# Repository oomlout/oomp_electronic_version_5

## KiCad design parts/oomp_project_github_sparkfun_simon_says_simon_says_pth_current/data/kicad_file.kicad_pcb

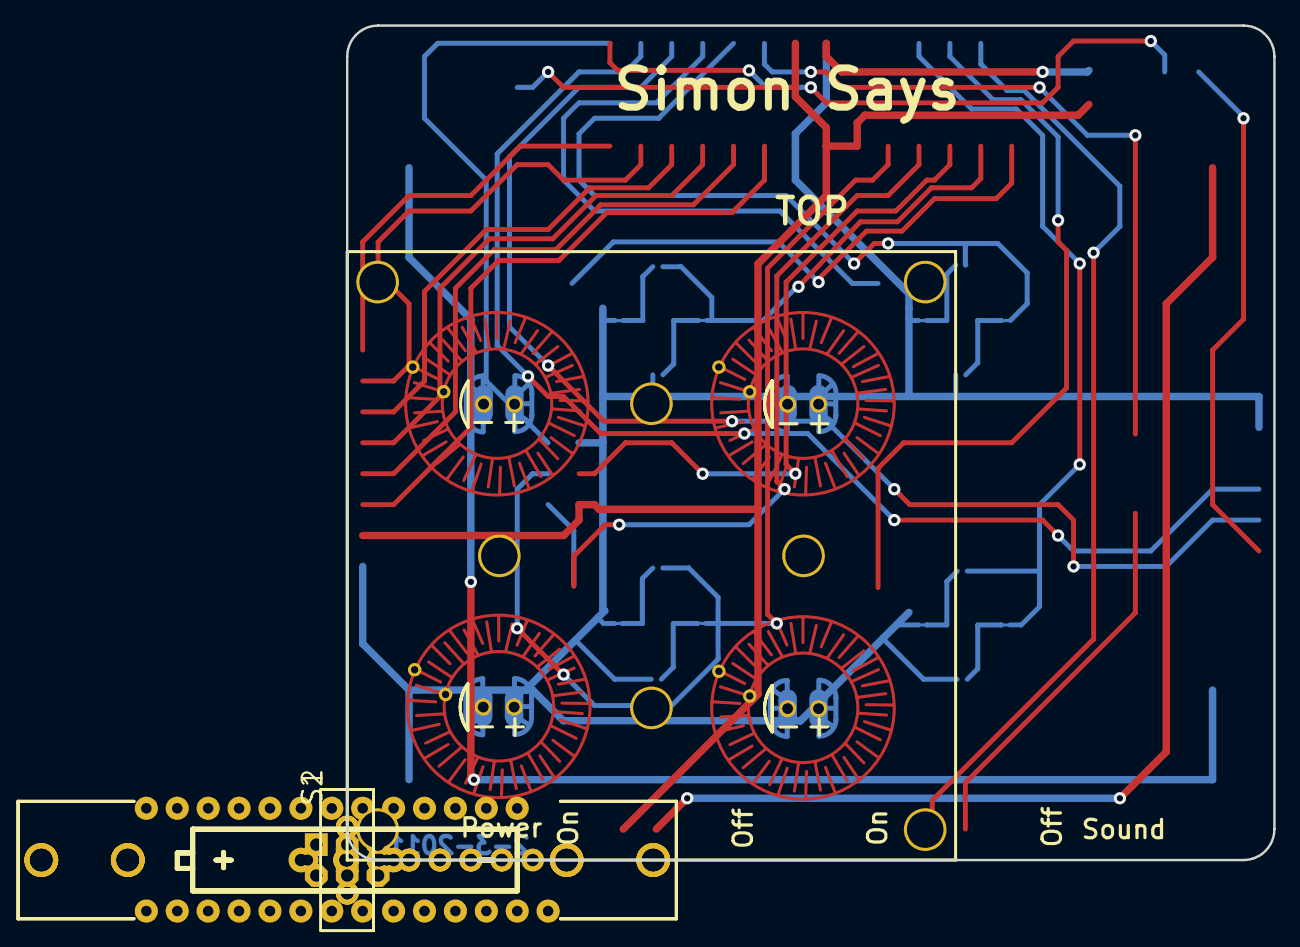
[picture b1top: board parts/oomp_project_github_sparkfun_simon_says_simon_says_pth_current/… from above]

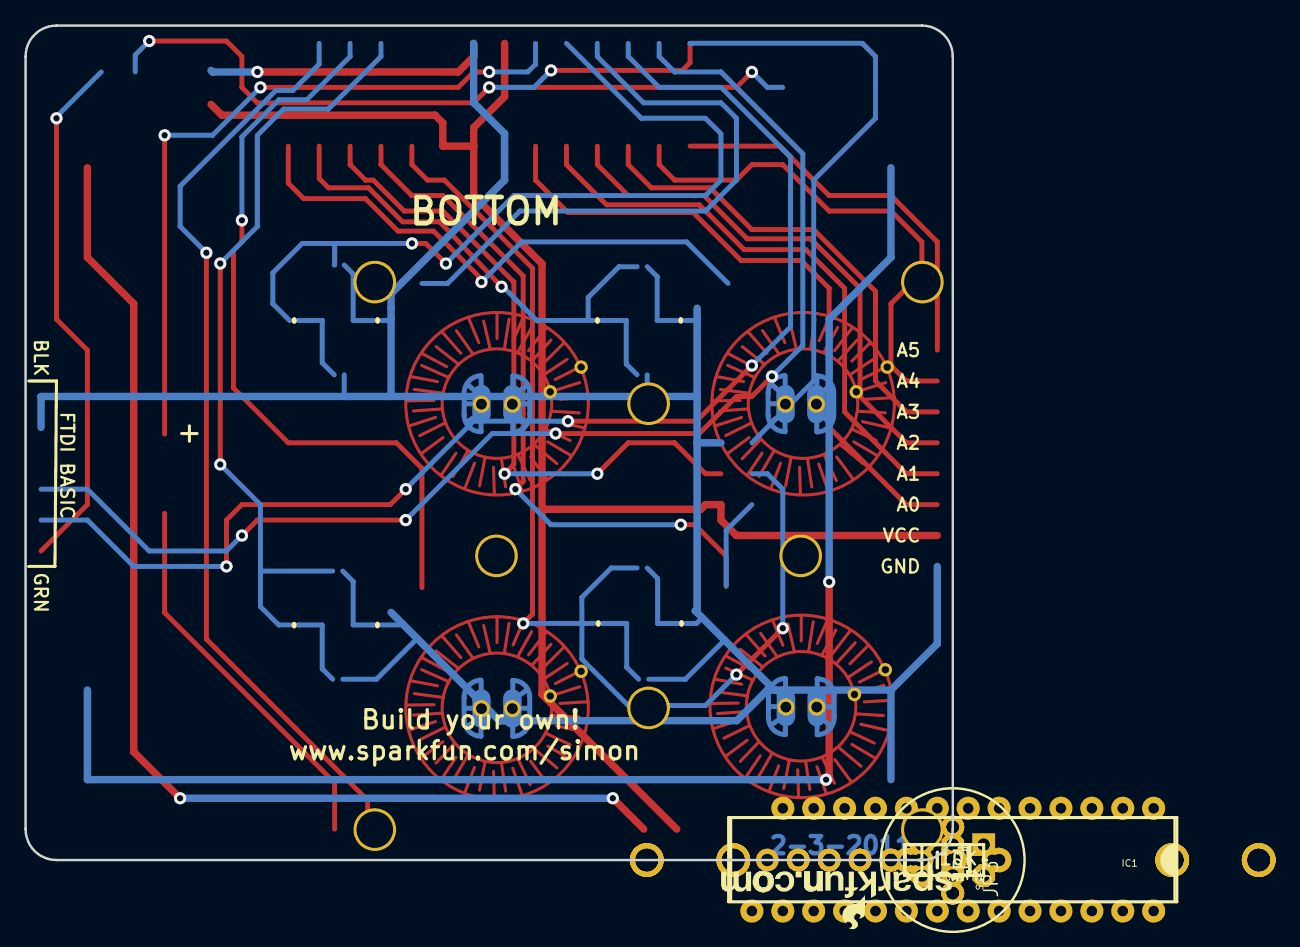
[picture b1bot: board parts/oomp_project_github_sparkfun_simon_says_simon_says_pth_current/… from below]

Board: 2 copper layers, 76.2 x 68.6 mm, 23 parts (17 on the bottom side), 26 nets.

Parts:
BAT1, BAT2: AA; BATTERY-AA-KIT
C1, C2: 0.1uF; CAP-PTH-SMALL-KIT
IC1: AVR-MEGA8-P; DIL28-3-SIMON-KIT
JP1: Serial; 1X06-NOSILK
JP2, JP5, JP6, JP7, JP8, JP9, JP10, JP11: SJ_2S_NO_SILK
JP3: AVR_SPI_PRG_6NS; 2X3-NS
JP4: 1X08NOSILK
P1-0: BUTTONPAD-2X2SINGLEKIT; BUTTONPAD-2X2SINGLE-KIT
R1: 10K; AXIAL-0.3-KIT
S1: Power; SWITCH-SPDT_KIT
S2: SWITCH-SPDT_KIT
SG1: BUZZER; BUZZER-12MM-KIT
U$1: LOGO-SFENEW; SFE-NEW-WEBLOGO
U$2: CREATIVE_COMMONS

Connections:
3.3V: C1.2, IC1.7, IC1.20, IC1.21, JP3.2, JP4.2, R1.P$2, S1.3
A0: IC1.23, JP4.3
A1: IC1.24, JP4.4
A2: IC1.25, JP4.5
A3: IC1.26, JP4.6
A4: IC1.27, JP4.7
A5: IC1.28, JP4.8
BUTTON_BLUE: IC1.18, JP3.1, P1-0.SIG1
BUTTON_GREEN: IC1.4, P1-0.SIG7
BUTTON_RED: IC1.15, P1-0.SIG5
BUTTON_YELLOW: IC1.12, P1-0.SIG3
BUZZER1: IC1.6, SG1.+
BUZZER2: IC1.13, S2.3
DTR: C2.1, JP1.1
GND: BAT1.GND@1, C1.1, IC1.8, IC1.22, JP1.5, JP1.6, JP2.1, JP3.6, JP4.1, JP5.2, JP6.2, JP7.1, JP8.2, JP9.1, JP10.2, JP11.1, P1-0.K1, P1-0.K2, P1-0.K3, P1-0.K4, P1-0.SIG2, P1-0.SIG4, P1-0.SIG6, P1-0.SIG8
LED_BLUE/SCK: IC1.19, JP3.3, JP8.1, JP9.2, P1-0.A1
LED_GREEN: IC1.5, JP6.1, JP7.2, P1-0.A4
LED_RED: IC1.16, JP2.2, JP5.1, P1-0.A3
LED_YELLOW: IC1.11, JP10.1, JP11.2, P1-0.A2
MOSI: IC1.17, JP3.4
unnamed: BAT2.PWR@1, S1.2
unnamed: S2.2, SG1.-
unnamed: BAT1.PWR@1, BAT2.GND@1
RESET: C2.2, IC1.1, JP3.5, R1.P$1
RX-I: IC1.2, JP1.3
TX-O: IC1.3, JP1.2

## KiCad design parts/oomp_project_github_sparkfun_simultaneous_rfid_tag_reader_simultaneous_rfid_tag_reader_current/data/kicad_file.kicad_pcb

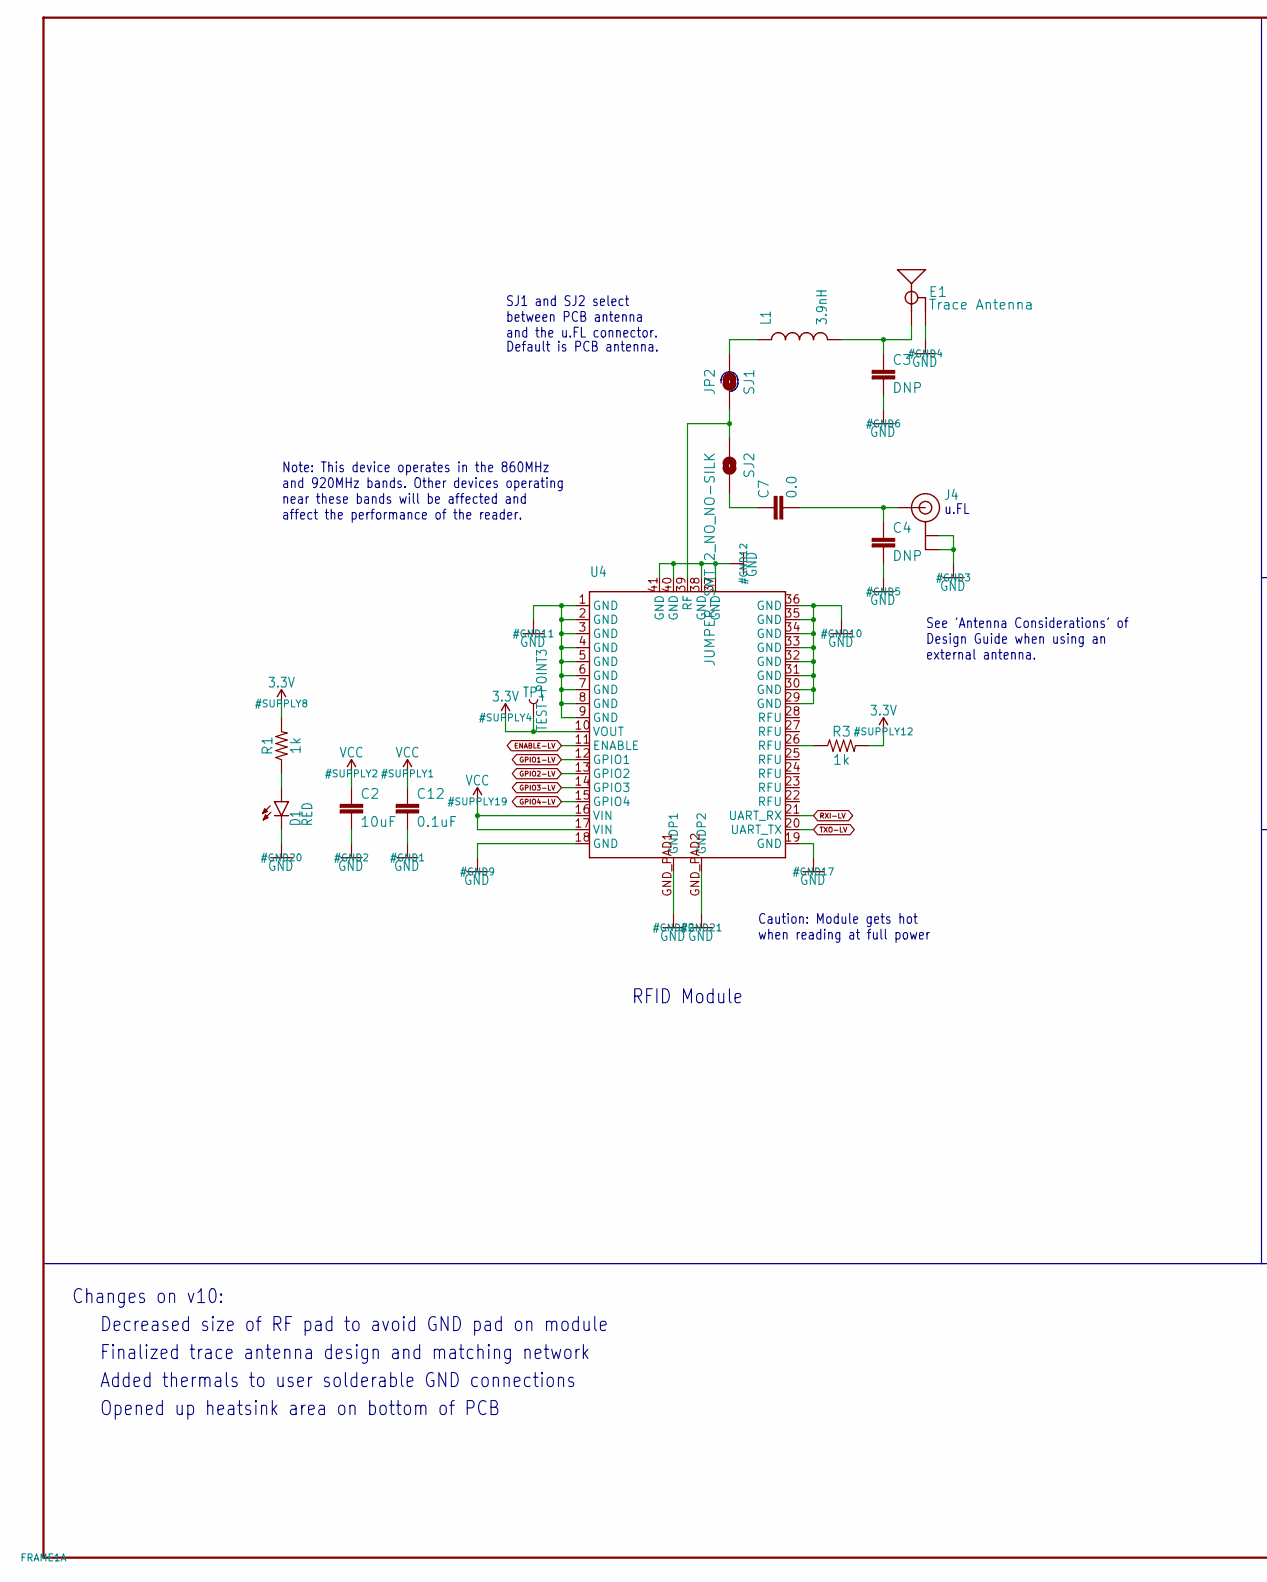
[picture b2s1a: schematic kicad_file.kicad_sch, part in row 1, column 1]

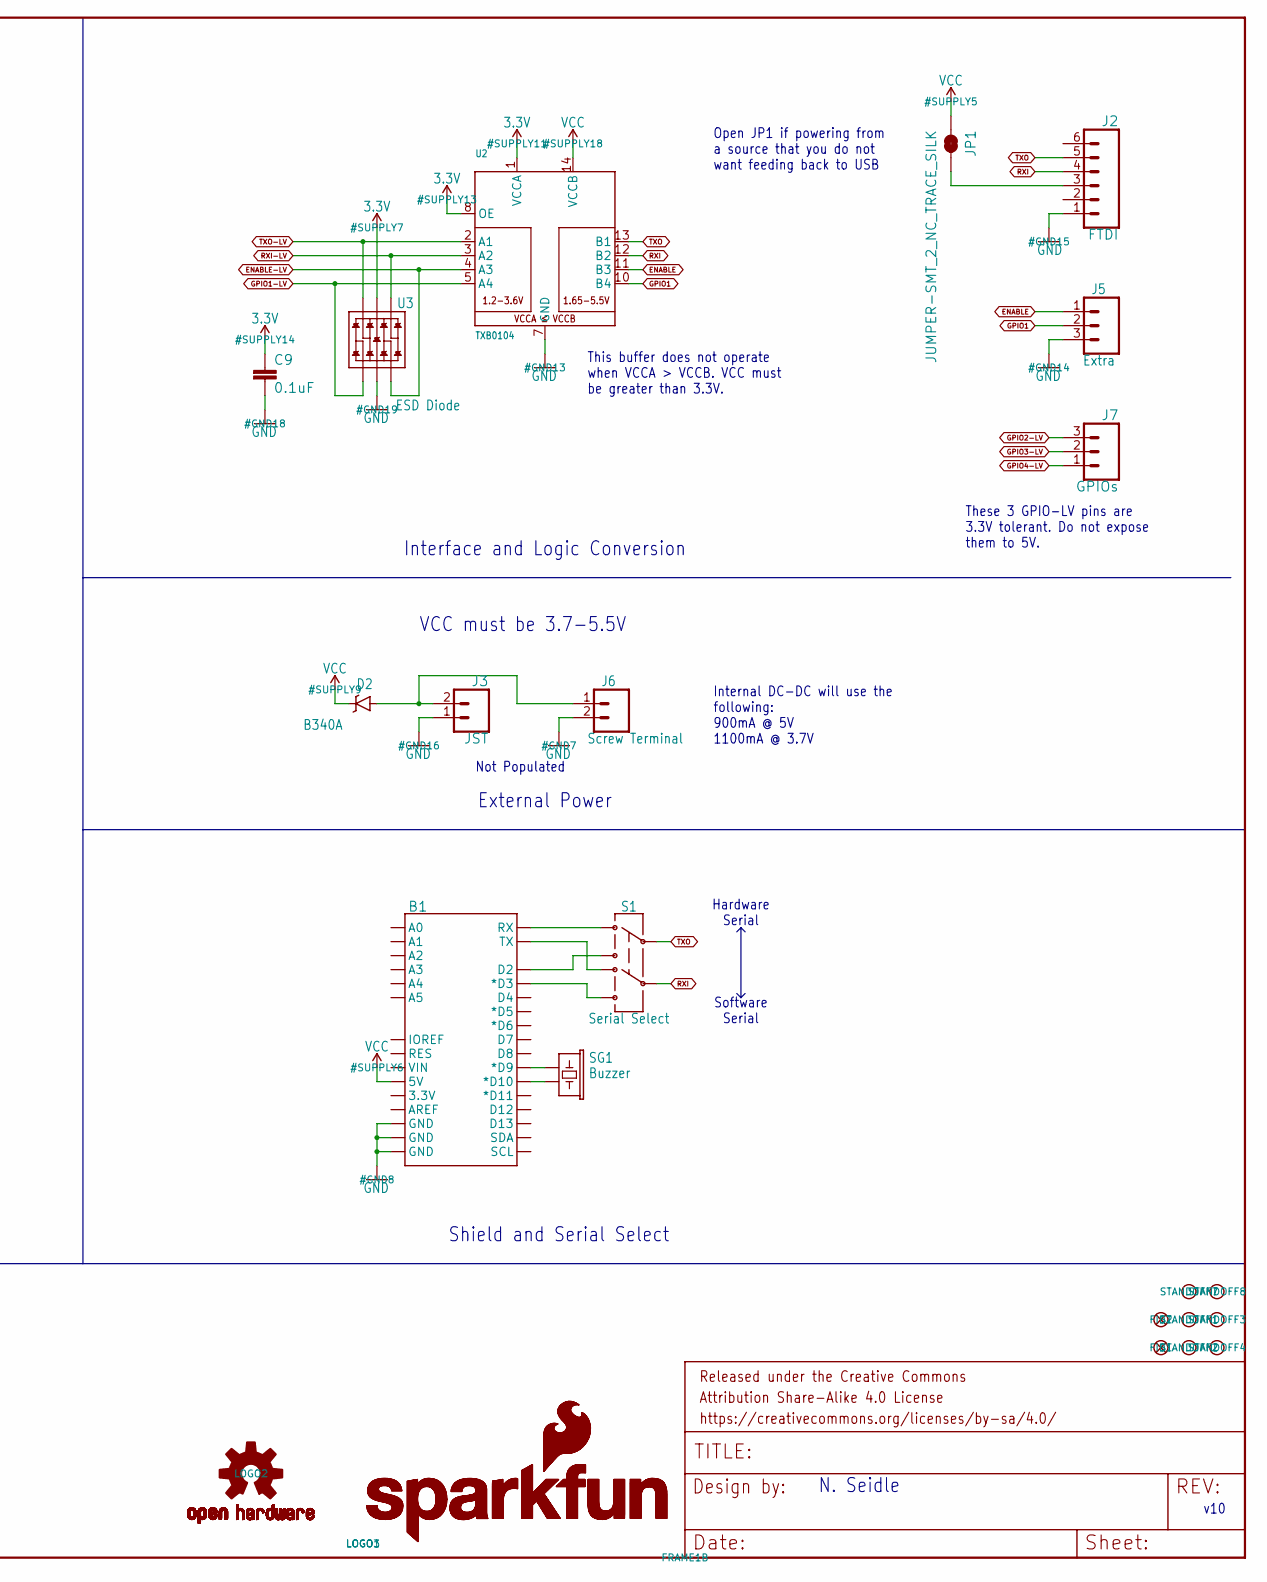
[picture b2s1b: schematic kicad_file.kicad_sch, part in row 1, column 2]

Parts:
B1: ARDUINO_UNO_SHIELD; UNO_R3_SHIELD
C2: 10uF; 0805
C3, C4: DNP; 0603
C7: 0.0; 0603
C9, C12: 0.1uF; 0603
D1: RED; LED-0603
D2: B340A; SMA-DIODE
E1: Trace Antenna; 915MHZ_ANTENNA_TRIMBLE
FID1, FID2: FIDUCIAL1X2; FIDUCIAL-1X2
FRAME1: FRAME-LEDGER; CREATIVE_COMMONS
J2: FTDI; 1X06
J3: JST; JST-2-PTH
J4: U.FL
J5: Extra; 1X03
J6: Screw Terminal; SCREWTERMINAL-3.5MM-2
J7: GPIOs; 1X03
JP1: JUMPER-SMT_2_NC_TRACE_SILK; SMT-JUMPER_2_NC_TRACE_SILK
JP2: SJ1; SMT-JUMPER_2_NO_NO-SILK
L1: 3.9nH; 0603
LOGO1, LOGO3: SFE_LOGO_NAME_FLAME.1_INCH; SFE_LOGO_NAME_FLAME_.1
LOGO2: OSHW-LOGOS; OSHW-LOGO-S
R1, R3: 1k; 0603
S1: Serial Select; SWITCH_DPDT_SMD_AYZ0202
SG1: Buzzer; BUZZER-CCV
SJ2: JUMPER-SMT_2_NO_NO-SILK; SMT-JUMPER_2_NO_NO-SILK
STANDOFF1, STANDOFF2, STANDOFF3, STANDOFF4, STANDOFF7, STANDOFF8: STAND-OFF
TP1: TEST-POINT3; PAD.03X.03
U2: TXB0104; SO14
U3: ESD Diode; SOT-23-6
U4: Nano; NANO_MODULE

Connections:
3.3V: C9.1, R1.2, R3.2, TP1.P$1, U2.1 (VCCA), U2.8 (OE), U3.5 (VCC), U4.10 (VOUT)
ANT3: JP2.1, SJ2.1, U4.39 (RF)
ENABLE: J5.1, U2.11 (B3)
ENABLE-LV: U2.4 (A3), U3.3 (IO2), U4.11 (ENABLE)
GND: B1.GND@0 (GND), B1.GND@1 (GND), B1.GND@2 (GND), C2.2, C3.2, C4.2, C9.2, C12.2, D1.C, E1.GND@1 (GND), E1.GND@2 (GND), E1.GND@3 (GND), J2.1, J3.1, J4.P$1 (GND), J4.P$2 (GND), J5.3, J6.2, U2.7 (GND), U3.2 (VSS), U4.1 (GND), U4.2 (GND), U4.3 (GND), U4.4 (GND), U4.5 (GND), U4.6 (GND), U4.7 (GND), U4.8 (GND), U4.9 (GND), U4.18 (GND), U4.19 (GND), U4.29 (GND), U4.30 (GND), U4.31 (GND), U4.32 (GND), U4.33 (GND), U4.34 (GND), U4.35 (GND), U4.36 (GND), U4.37 (GND), U4.38 (GND), U4.40 (GND), U4.41 (GND), U4.GND_PAD1 (GNDP1), U4.GND_PAD2 (GNDP2)
GPIO1: J5.2, U2.10 (B4)
GPIO1-LV: U2.5 (A4), U3.1 (IO1), U4.12 (GPIO1)
GPIO2-LV: J7.3, U4.13 (GPIO2)
GPIO3-LV: J7.2, U4.14 (GPIO3)
GPIO4-LV: J7.1, U4.15 (GPIO4)
unnamed: C3.1, E1.ANT (SIGNAL), L1.2
unnamed: JP2.2, L1.1
unnamed: C7.1, SJ2.2
unnamed: R3.1, U4.26 (RFU)
unnamed: C4.1, C7.2, J4.P$3 (SIGNAL)
unnamed: D1.A, R1.1
unnamed: J2.3, JP1.2
unnamed: B1.RX, S1.1
unnamed: B1.TX, S1.4
unnamed: B1.D9 (*D9), SG1.+ (1)
unnamed: D2.A, J3.2, J6.1
unnamed: B1.D10 (*D10), SG1.- (2)
RXI: J2.4, S1.5, U2.12 (B2)
RXI-LV: U2.3 (A2), U3.4 (IO3), U4.21 (UART_RX)
SOFT-RX: B1.D2, S1.3
SOFT-TX: B1.D3 (*D3), S1.6
TXO: J2.5, S1.2, U2.13 (B1)
TXO-LV: U2.2 (A1), U3.6 (IO4), U4.20 (UART_TX)
VCC: B1.5V, C2.1, C12.1, D2.C, JP1.1, U2.14 (VCCB), U4.16 (VIN), U4.17 (VIN)

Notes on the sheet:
Default is PCB antenna.
This buffer does not operate when VCCA > VCCB. VCC must be greater than 3.3V.
Opened up heatsink area on bottom of PCB
Not Populated
External Power
Open JP1 if powering from a source that you do not want feeding back to USB
Shield and Serial Select
Caution: Module gets hot when reading at full power
Added thermals to user solderable GND connections
v10
RFID Module
Hardware Serial
SJ1 and SJ2 select between PCB antenna and the u.FL connector.
N. Seidle
Note: This device operates in the 860MHz and 920MHz bands. Other devices operating near these bands will be affected and affect the performance of the reader.
Finalized trace antenna design and matching network
u.FL
VCC must be 3.7-5.5V
Decreased size of RF pad to avoid GND pad on module
Internal DC-DC will use the following: 900mA @ 5V 1100mA @ 3.7V
These 3 GPIO-LV pins are 3.3V tolerant. Do not expose them to 5V.
Software Serial
Changes on v10:
Interface and Logic Conversion
See 'Antenna Considerations' of Design Guide when using an external antenna.

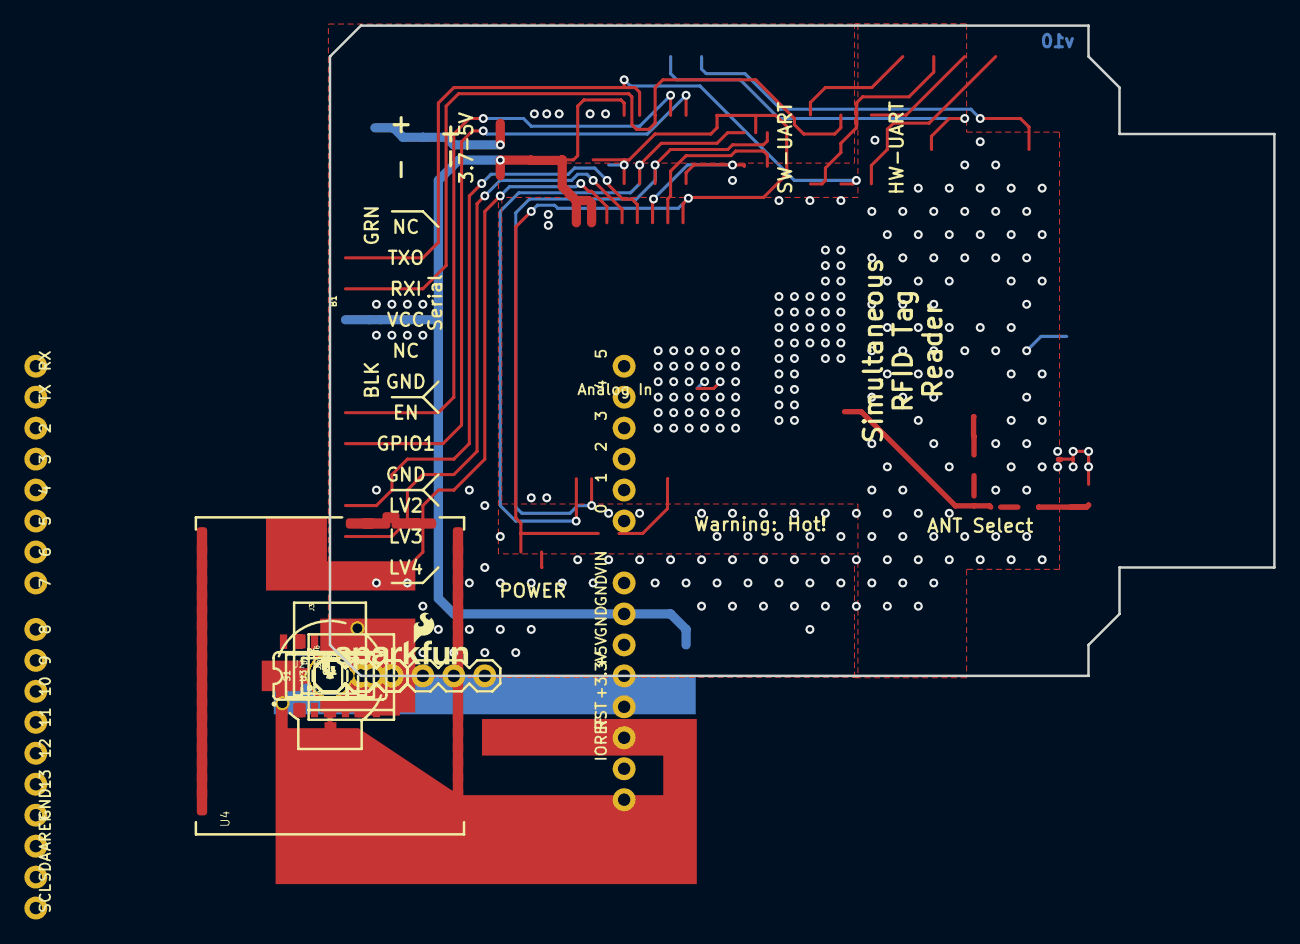
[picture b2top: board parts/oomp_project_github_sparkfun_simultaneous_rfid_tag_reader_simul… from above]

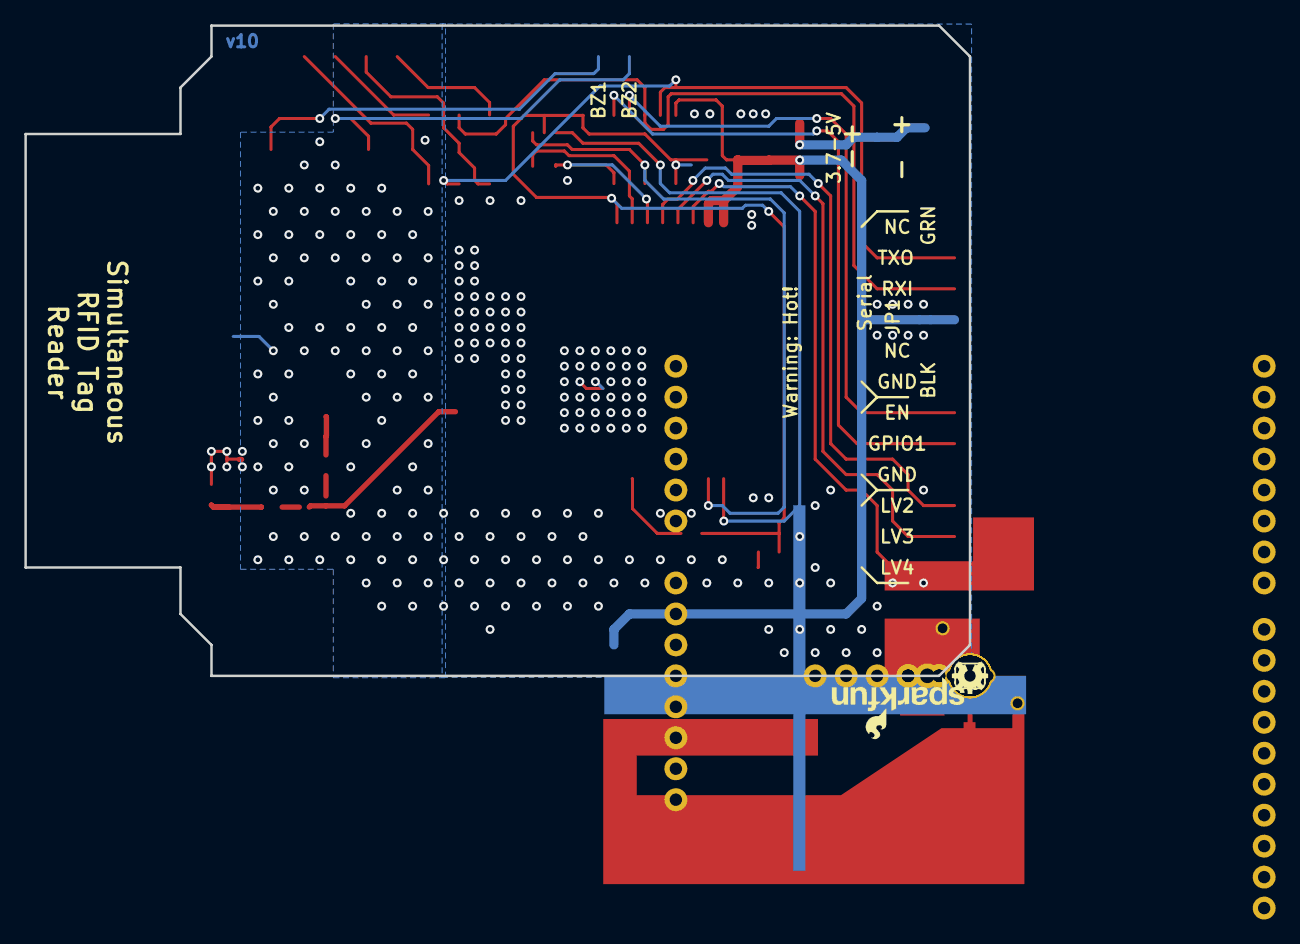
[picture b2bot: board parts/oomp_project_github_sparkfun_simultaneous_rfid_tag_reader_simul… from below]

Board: 2 copper layers, 77.5 x 53.3 mm, 40 parts (4 on the bottom side), 29 nets.

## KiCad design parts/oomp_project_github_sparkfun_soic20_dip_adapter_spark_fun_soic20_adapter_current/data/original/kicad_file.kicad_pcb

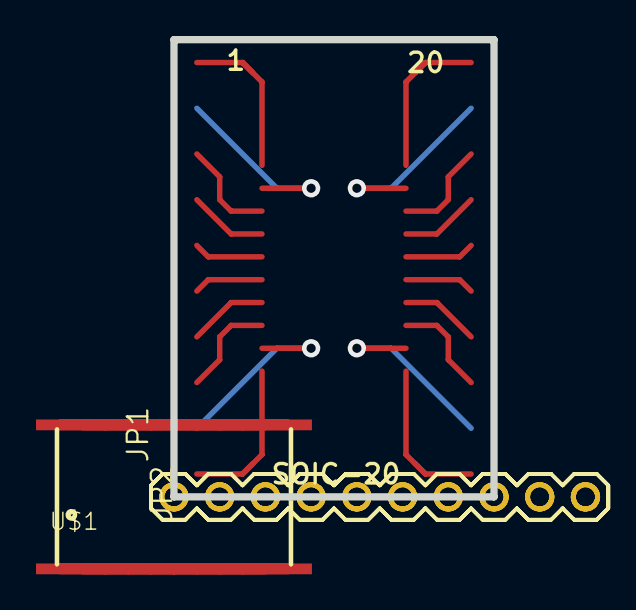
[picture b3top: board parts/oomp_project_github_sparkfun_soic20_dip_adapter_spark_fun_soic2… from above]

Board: 16 copper layers, 17.8 x 25.4 mm, 4 parts (1 on the bottom side), 20 nets.

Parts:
JP1, JP2: M100.1; 1X10
U$1: SOIC_20; SO20W
U$2: LOGO-SFENEW; SFE-NEW-WEBLOGO

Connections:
unnamed: JP1.1, U$1.P$10
unnamed: JP1.2, U$1.P$9
unnamed: JP1.3, U$1.P$8
unnamed: JP1.4, U$1.P$7
unnamed: JP1.5, U$1.P$6
unnamed: JP1.6, U$1.P$5
unnamed: JP1.7, U$1.P$4
unnamed: JP1.8, U$1.P$3
unnamed: JP1.9, U$1.P$2
unnamed: JP1.10, U$1.P$1
unnamed: JP2.1, U$1.P$20
unnamed: JP2.2, U$1.P$19
unnamed: JP2.3, U$1.P$18
unnamed: JP2.4, U$1.P$17
unnamed: JP2.5, U$1.P$16
unnamed: JP2.6, U$1.P$15
unnamed: JP2.7, U$1.P$14
unnamed: JP2.8, U$1.P$13
unnamed: JP2.9, U$1.P$12
unnamed: JP2.10, U$1.P$11

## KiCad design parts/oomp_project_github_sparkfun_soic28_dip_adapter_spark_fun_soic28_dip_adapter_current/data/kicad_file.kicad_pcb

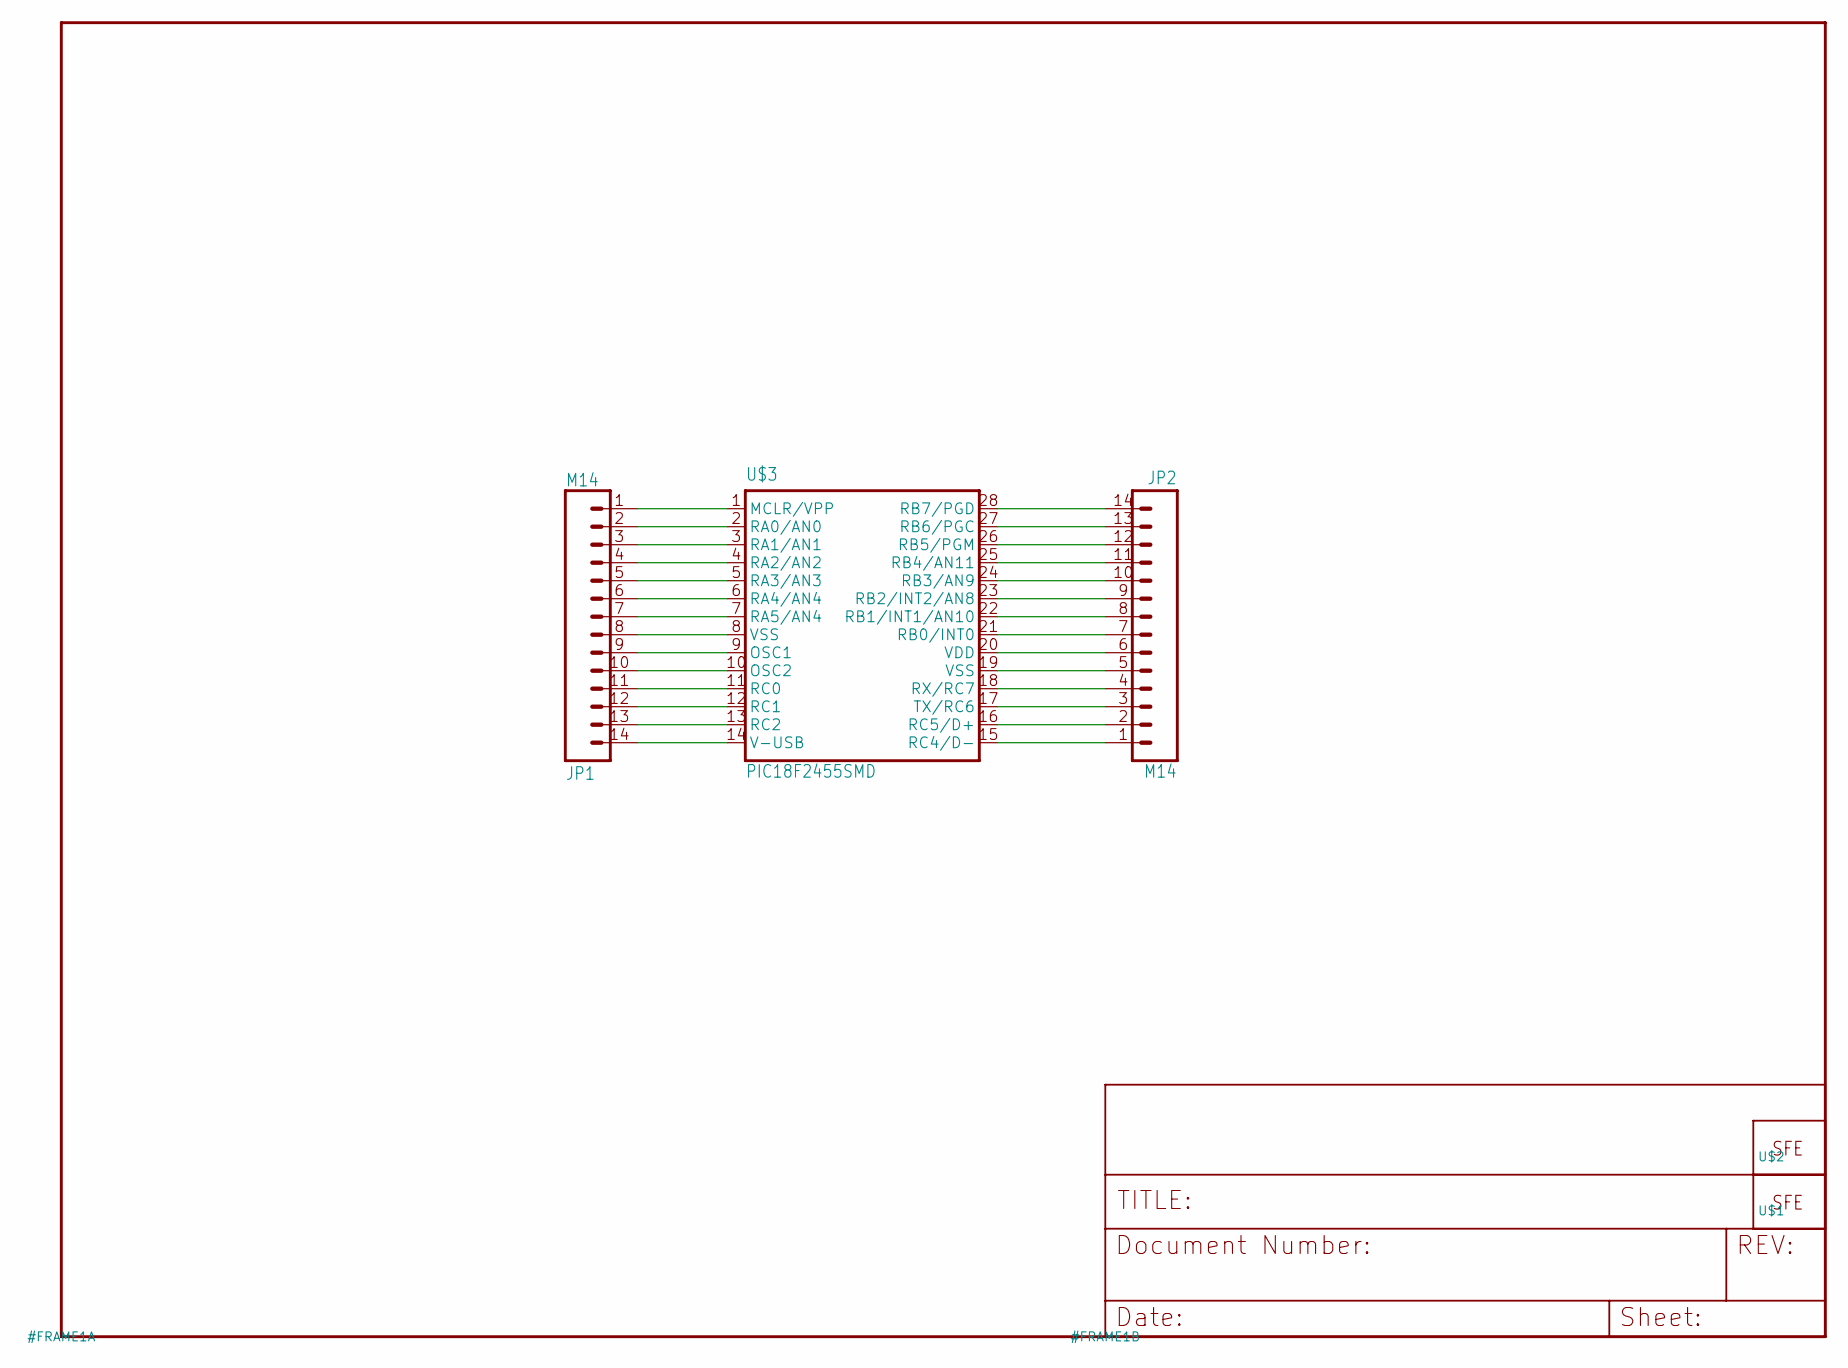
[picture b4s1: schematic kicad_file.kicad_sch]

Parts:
JP1, JP2: M14; 1X14
U$1: LOGO-SFESK; SFE-LOGO-FLAME
U$2: LOGO-SFENEW; SFE-NEW-WEBLOGO
U$3: PIC18F2455SMD; SO-28W

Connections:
unnamed: JP1.1, U$3.1 (MCLR/VPP)
unnamed: JP1.2, U$3.2 (RA0/AN0)
unnamed: JP1.3, U$3.3 (RA1/AN1)
unnamed: JP1.4, U$3.4 (RA2/AN2)
unnamed: JP1.5, U$3.5 (RA3/AN3)
unnamed: JP1.6, U$3.6 (RA4/AN4)
unnamed: JP1.7, U$3.7 (RA5/AN4)
unnamed: JP1.8, U$3.8 (VSS)
unnamed: JP1.9, U$3.9 (OSC1)
unnamed: JP1.10, U$3.10 (OSC2)
unnamed: JP1.11, U$3.11 (RC0)
unnamed: JP1.12, U$3.12 (RC1)
unnamed: JP1.13, U$3.13 (RC2)
unnamed: JP1.14, U$3.14 (V-USB)
unnamed: JP2.1, U$3.15 (RC4/D-)
unnamed: JP2.2, U$3.16 (RC5/D+)
unnamed: JP2.3, U$3.17 (TX/RC6)
unnamed: JP2.4, U$3.18 (RX/RC7)
unnamed: JP2.5, U$3.19 (VSS)
unnamed: JP2.6, U$3.20 (VDD)
unnamed: JP2.7, U$3.21 (RB0/INT0)
unnamed: JP2.8, U$3.22 (RB1/INT1/AN10)
unnamed: JP2.9, U$3.23 (RB2/INT2/AN8)
unnamed: JP2.10, U$3.24 (RB3/AN9)
unnamed: JP2.11, U$3.25 (RB4/AN11)
unnamed: JP2.12, U$3.26 (RB5/PGM)
unnamed: JP2.13, U$3.27 (RB6/PGC)
unnamed: JP2.14, U$3.28 (RB7/PGD)

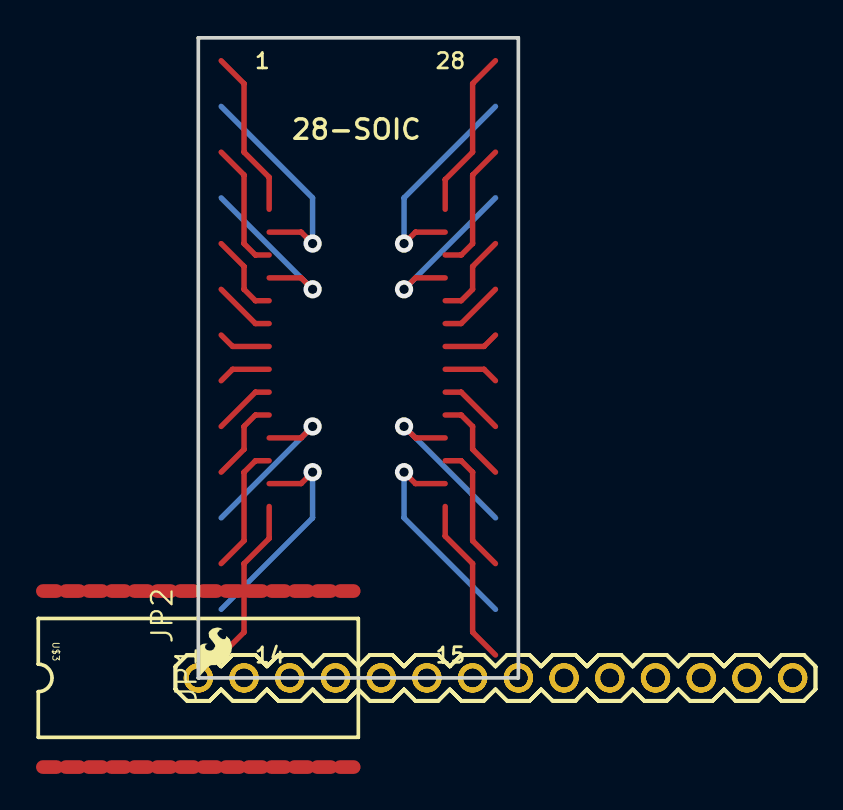
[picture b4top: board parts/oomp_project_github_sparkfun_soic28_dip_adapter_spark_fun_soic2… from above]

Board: 2 copper layers, 17.8 x 35.6 mm, 5 parts (1 on the bottom side), 28 nets.

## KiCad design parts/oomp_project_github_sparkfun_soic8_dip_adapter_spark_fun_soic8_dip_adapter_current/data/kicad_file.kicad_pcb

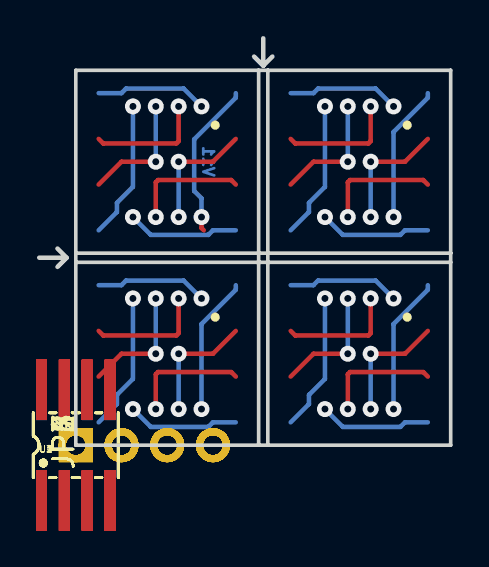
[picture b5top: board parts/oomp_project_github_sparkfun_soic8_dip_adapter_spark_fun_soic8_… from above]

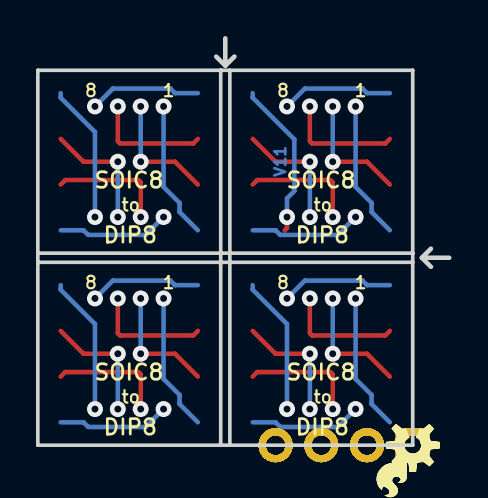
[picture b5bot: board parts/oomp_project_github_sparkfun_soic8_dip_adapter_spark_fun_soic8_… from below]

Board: 2 copper layers, 22.9 x 22.6 mm, 17 parts (4 on the bottom side), 32 nets.

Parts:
FRAME1: frame; CREATIVE_COMMONS
JP1, JP3, JP5, JP7: 1x4; 1X04_NO_SILK
JP2, JP4, JP6, JP8: 1x4; 1X04_NO_SILK_ALL_ROUND
LOGO1: SFE_LOGO_FLAME.1_INCH; SFE_LOGO_FLAME_.1
LOGO2, LOGO3: OSHW-LOGOS; OSHW-LOGO-S
LOGO4: SFE_LOGO_FLAME.1_INCH; SFE_LOGO_FLAME_.1@1
U1, U2, U3, U4: GENERIC-SOIC8; SO08-UNIVERSAL

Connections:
unnamed: JP1.1, U1.1
unnamed: JP1.2, U1.2
unnamed: JP1.3, U1.3
unnamed: JP1.4, U1.4
unnamed: JP2.1, U1.8
unnamed: JP2.2, U1.7
unnamed: JP2.3, U1.6
unnamed: JP2.4, U1.5
unnamed: JP3.1, U2.1
unnamed: JP3.2, U2.2
unnamed: JP3.3, U2.3
unnamed: JP3.4, U2.4
unnamed: JP4.1, U2.8
unnamed: JP4.2, U2.7
unnamed: JP4.3, U2.6
unnamed: JP4.4, U2.5
unnamed: JP5.1, U3.1
unnamed: JP5.2, U3.2
unnamed: JP5.3, U3.3
unnamed: JP5.4, U3.4
unnamed: JP6.4, U3.5
unnamed: JP6.3, U3.6
unnamed: JP6.2, U3.7
unnamed: JP6.1, U3.8
unnamed: JP7.1, U4.1
unnamed: JP7.2, U4.2
unnamed: JP7.3, U4.3
unnamed: JP7.4, U4.4
unnamed: JP8.1, U4.8
unnamed: JP8.2, U4.7
unnamed: JP8.3, U4.6
unnamed: JP8.4, U4.5

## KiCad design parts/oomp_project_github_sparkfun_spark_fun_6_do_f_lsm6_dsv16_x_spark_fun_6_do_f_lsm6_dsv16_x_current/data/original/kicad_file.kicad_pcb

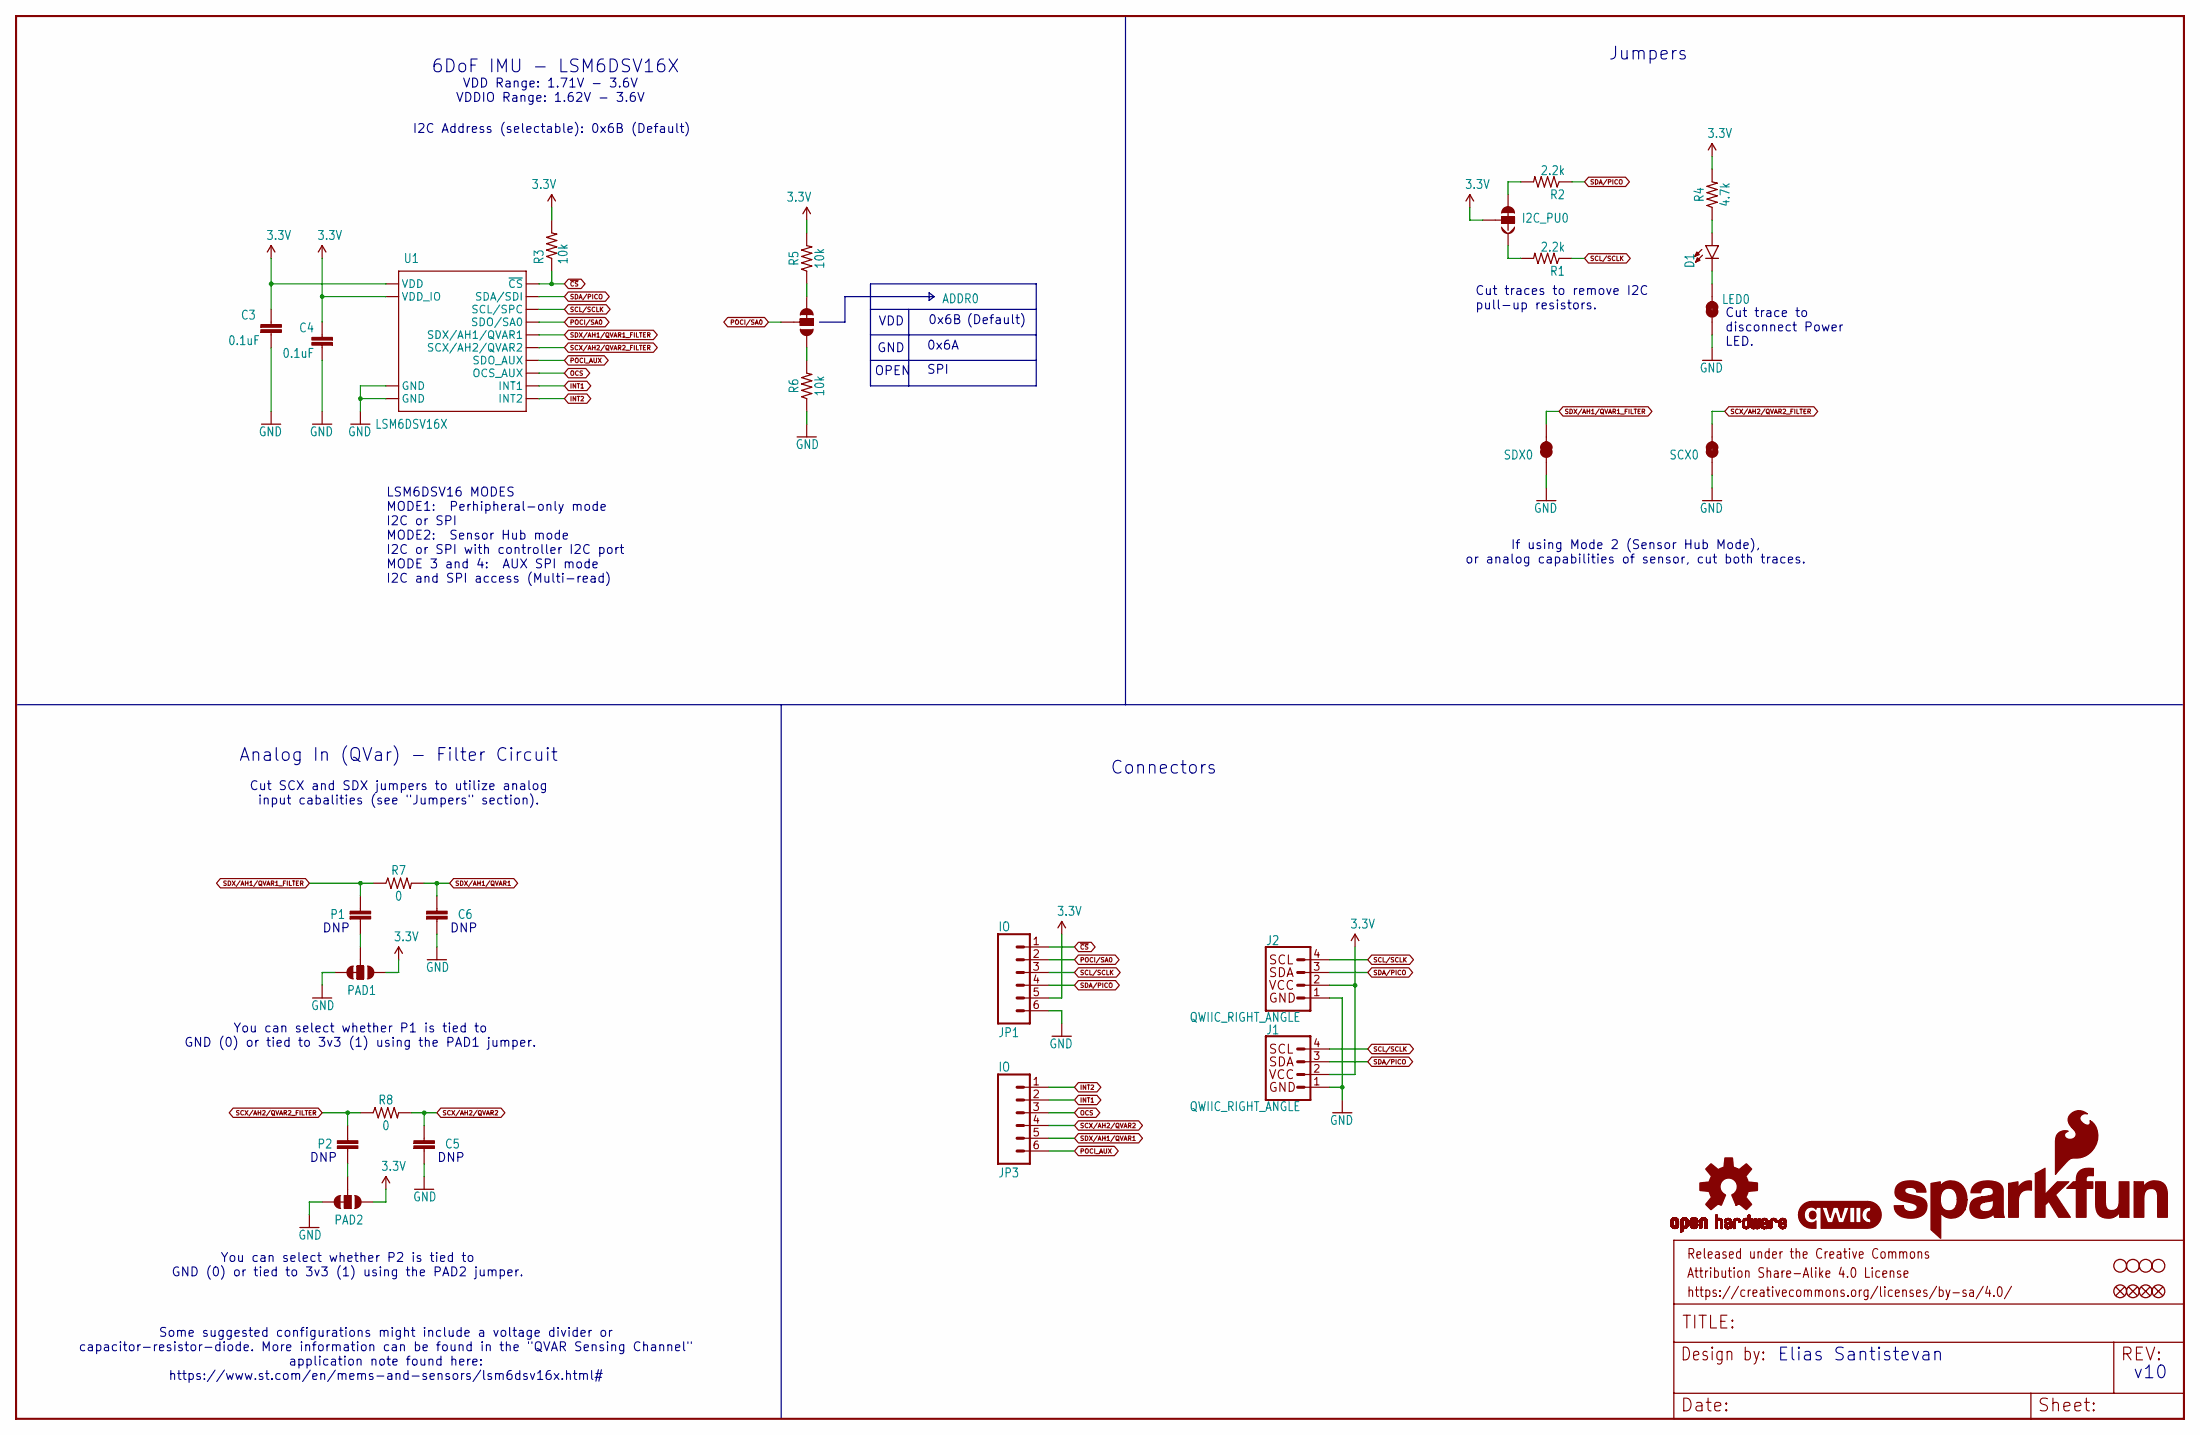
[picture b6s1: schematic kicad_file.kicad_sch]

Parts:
ADDR0: JUMPER-SMT_3_1-NC_TRACE_SILK; SMT-JUMPER_3_1-NC_TRACE_SILK
C3, C4: 0.1uF; 0603
C5, C6: 110pF; 0603
D1: RED; LED-0603
FD1, FD2: FIDUCIALUFIDUCIAL; FIDUCIAL-MICRO
FID1, FID2: FIDUCIALUFIDUCIAL; FIDUCIAL-MICRO
FRAME2: FRAME-LEDGER; CREATIVE_COMMONS
I2C_PU0: S_MODE; SMT-JUMPER_3_2-NC_TRACE_SILK
J1, J2: QWIIC_RIGHT_ANGLE; JST04_1MM_RA
JP1, JP3: IO; 1X06_NO_SILK
LED0: JUMPER-SMT_2_NC_TRACE_SILK; SMT-JUMPER_2_NC_TRACE_SILK
LOGO1: QWIIC_LOGO_4MM; QWIIC_4MM
LOGO2: OSHW-LOGOMINI; OSHW-LOGO-MINI
LOGO3: SFE_LOGO_NAME_FLAMEBLANK; BLANK
P1, P2: 110pF; 0603
PAD1, PAD2: JUMPER-SMT_3_1-NC_TRACE_SILK; SMT-JUMPER_3_1-NC_TRACE_SILK
R1, R2: 2.2k; 0603
R3, R5, R6: 10k; 0603
R4: 4.7k; 0603
R7, R8: 0; 0603
SCX0: JUMPER-SMT_2_NC_TRACE_SILK; SMT-JUMPER_2_NC_TRACE_SILK
SDX0: JUMPER-SMT_2_NC_TRACE_SILK; SMT-JUMPER_2_NC_TRACE_SILK
STANDOFF1, STANDOFF2, STANDOFF3, STANDOFF4: STAND-OFFTIGHT; STAND-OFF-TIGHT
U1: LSM6DSV16X; LGA-14L

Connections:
3.3V: C3.1, C4.1, I2C_PU0.2, J1.2, J2.2, JP1.5, PAD1.1, PAD2.1, R3.2, R4.2, R5.2, U1.P5 (VDD_IO), U1.P8 (VDD)
GND: C3.2, C4.2, C5.2, C6.2, J1.1, J2.1, JP1.6, LED0.1, PAD1.3, PAD2.3, R6.1, SCX0.1, SDX0.1, U1.P6 (GND), U1.P7 (GND)
INT1: JP3.2, U1.P4 (INT1)
INT2: JP3.1, U1.P9 (INT2)
unnamed: ADDR0.3, R5.1
unnamed: D1.A, R4.1
unnamed: D1.C, LED0.2
unnamed: P2.2, PAD2.2
unnamed: I2C_PU0.1, R1.2
unnamed: I2C_PU0.3, R2.2
unnamed: ADDR0.1, R6.2
unnamed: P1.2, PAD1.2
OCS: JP3.3, U1.P10 (OCS_AUX)
POCI/SA0: ADDR0.2, JP1.2, U1.P1 (SDO/SA0)
POCI_AUX: JP3.6, U1.P11 (SDO_AUX)
SCL/SCLK: J1.4, J2.4, JP1.3, R1.1, U1.P13 (SCL/SPC)
SCX/AH2/QVAR2: C5.1, JP3.4, R8.2
SCX/AH2/QVAR2_FILTER: P2.1, R8.1, SCX0.2, U1.P3 (SCX/AH2/QVAR2)
SDA/PICO: J1.3, J2.3, JP1.4, R2.1, U1.P14 (SDA/SDI)
SDX/AH1/QVAR1: C6.1, JP3.5, R7.2
SDX/AH1/QVAR1_FILTER: P1.1, R7.1, SDX0.2, U1.P2 (SDX/AH1/QVAR1)
~CS: JP1.1, R3.1, U1.P12 (~CS)

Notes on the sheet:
Jumpers
v10
DNP
Elias Santistevan
OPEN
0x6A
Cut SCX and SDX jumpers to utilize analog input cabalities (see "Jumpers" section).
VDD Range: 1.71V - 3.6V VDDIO Range: 1.62V - 3.6V
Analog In (QVar) - Filter Circuit
6DoF IMU - LSM6DSV16X
Some suggested configurations might include a voltage divider or capacitor-resistor-diode. More information can be found in the "QVAR Sensing Channel" application note found here: https://www.st.com/en/mems-and-sensors/lsm6dsv16x.html#
(Default)
You can select whether P2 is tied to GND (0) or tied to 3v3 (1) using the PAD2 jumper.
LSM6DSV16 MODES MODE1: Perhipheral-only mode I2C or SPI MODE2: Sensor Hub mode I2C or SPI with controller I2C port MODE 3 and 4: AUX SPI mode I2C and SPI access (Multi-read)
I2C Address (selectable): 0x6B (Default)
SPI
Cut trace to disconnect Power LED.
0x6B
VDD
GND
If using Mode 2 (Sensor Hub Mode), or analog capabilities of sensor, cut both traces.
Connectors
You can select whether P1 is tied to GND (0) or tied to 3v3 (1) using the PAD1 jumper.
Cut traces to remove I2C pull-up resistors.

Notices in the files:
parts/oomp_project_github_sparkfun_simon_says_simon_says_pth_current/data/kicad_file.kicad_sch:
Released under the Creative Commons Attribution Share-Alike 3.0 License
http://creativecommons.org/licenses/by-sa/3.0
parts/oomp_project_github_sparkfun_simultaneous_rfid_tag_reader_simultaneous_rfid_tag_reader_current/data/original/kicad_file.kicad_sch:
https://creativecommons.org/licenses/by-sa/4.0
parts and their libraries:
Released under the Creative Commons Attribution Share-Alike 4.0 License
